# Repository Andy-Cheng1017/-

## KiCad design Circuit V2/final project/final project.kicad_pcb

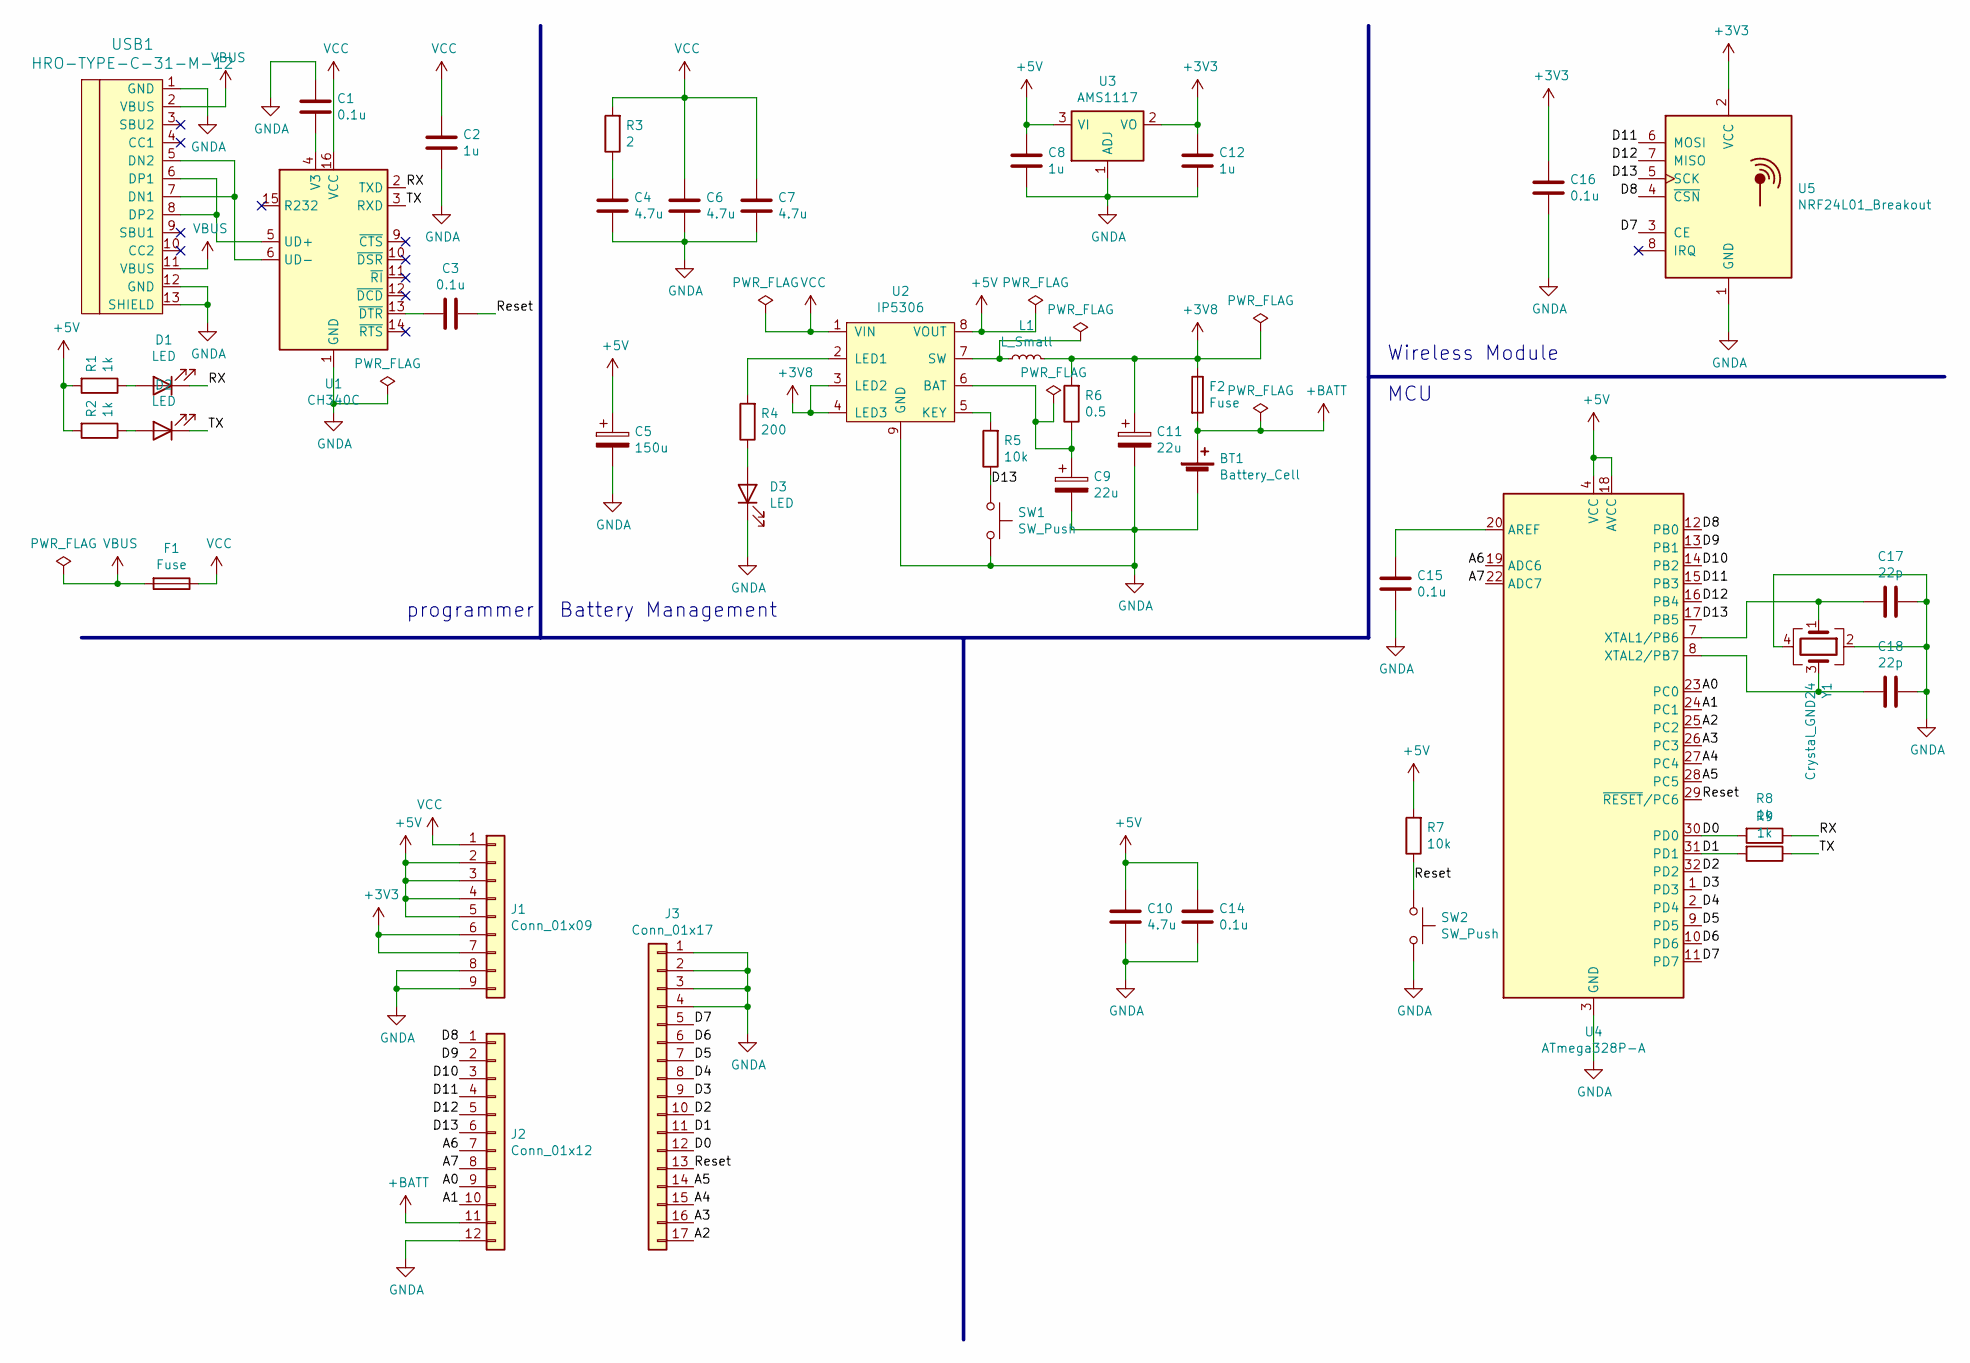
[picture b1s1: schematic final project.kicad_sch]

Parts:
BT1: Battery_Cell; BatteryHolder_MPD_BH-18650-PC2
C1, C3, C14, C15, C16: 0.1u; C_0805_2012Metric
C2, C8, C12: 1u; C_0805_2012Metric
C4, C6, C7, C10: 4.7u; C_0805_2012Metric
C5: 150u; CP_EIA-7343-15_Kemet-W
C9, C11: 22u; CP_EIA-7343-15_Kemet-W
C17, C18: 22p; C_0805_2012Metric
D1, D2, D3: LED; LED_0805_2012Metric
F1, F2: Fuse; Fuse_1812_4532Metric
J1: Conn_01x09; PinHeader_1x09_P2.54mm_Vertical
J2: Conn_01x12; PinHeader_1x12_P2.54mm_Vertical
J3: Conn_01x17; PinHeader_1x17_P2.54mm_Vertical
L1: L_Small; L_Bourns_SRN6045TA
R1, R2, R8, R9: 1k; R_0805_2012Metric
R3: 2; R_0805_2012Metric
R4: 200; R_0805_2012Metric
R5, R7: 10k; R_0805_2012Metric
R6: 0.5; R_0805_2012Metric
SW1, SW2: SW_Push; SW_SPST_CK_RS282G05A3
U1: CH340C; SOIC-16_3.9x9.9mm_P1.27mm
U2: IP5306; SOIC-8-1EP_3.9x4.9mm_P1.27mm_EP2.29x3mm_ThermalVias
U3: AMS1117; SOT-223-3_TabPin2
U4: ATmega328P-A; TQFP-32_7x7mm_P0.8mm
U5: NRF24L01_Breakout; NRF24L01-SMD
USB1: HRO-TYPE-C-31-M-12
Y1: Crystal_GND24; Crystal_SMD_3225-4Pin_3.2x2.5mm

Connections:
+3V3: C12.2, C16.2, J1.6, J1.7, U3.2 (VO), U5.2 (VCC)
+3V8: C11.1, F2.1, L1.2, R6.2, U2.3 (LED2), U2.4 (LED3)
+5V: C5.1, C8.2, C10.2, C14.2, J1.2, J1.3, J1.4, J1.5, R1.2, R2.2, R7.2, U2.8 (VOUT), U3.3 (VI), U4.4 (VCC), U4.6 (VCC), U4.18 (AVCC)
+BATT: BT1.1 (+), F2.2, J2.11
/A0: J2.9, U4.23 (PC0)
/A1: J2.10, U4.24 (PC1)
/A2: J3.17, U4.25 (PC2)
/A3: J3.16, U4.26 (PC3)
/A4: J3.15, U4.27 (PC4)
/A5: J3.14, U4.28 (PC5)
/A6: J2.7, U4.19 (ADC6)
/A7: J2.8, U4.22 (ADC7)
/D0: J3.12, R8.2, U4.30 (PD0)
/D1: J3.11, R9.2, U4.31 (PD1)
/D2: J3.10, U4.32 (PD2)
/D3: J3.9, U4.1 (PD3)
/D4: J3.8, U4.2 (PD4)
/D5: J3.7, U4.9 (PD5)
/D6: J3.6, U4.10 (PD6)
/D7: J3.5, U4.11 (PD7), U5.3 (CE)
/D8: J2.1, U4.12 (PB0), U5.4 (~CSN)
/D9: J2.2, U4.13 (PB1)
/D10: J2.3, U4.14 (PB2)
/D11: J2.4, U4.15 (PB3), U5.6 (MOSI)
/D12: J2.5, U4.16 (PB4), U5.7 (MISO)
/D13: J2.6, R5.1, SW1.1, U4.17 (PB5), U5.5 (SCK)
/RX: D1.1 (K), R8.1, U1.2 (TXD)
/Reset: C3.1, J3.13, R7.1, SW2.1, U4.29 (~RESET/PC6)
/TX: D2.1 (K), R9.1, U1.3 (RXD)
GNDA: BT1.2 (-), C1.2, C2.1, C4.1, C5.2, C6.1, C7.1, C8.1, C9.2, C10.1, C11.2, C12.1, C14.1, C15.1, C16.1, C17.1, C18.1, D3.1 (K), J1.8, J1.9, J2.12, J3.1, J3.2, J3.3, J3.4, SW1.2, SW2.2, U1.1 (GND), U2.9 (GND), U3.1 (ADJ), U4.3 (GND), U4.5 (GND), U4.21 (GND), U5.1 (GND), USB1.1 (GND), USB1.12 (GND), USB1.13 (SHIELD), Y1.2, Y1.4
unnamed: C1.1, U1.4 (V3)
unnamed: C3.2, U1.13 (~DTR)
unnamed: C4.2, R3.1
unnamed: C9.1, R6.1, U2.6 (BAT)
unnamed: C15.2, U4.20 (AREF)
unnamed: C17.2, U4.7 (XTAL1/PB6), Y1.1
unnamed: C18.2, U4.8 (XTAL2/PB7), Y1.3
unnamed: D1.2 (A), R1.1
unnamed: D2.2 (A), R2.1
unnamed: D3.2 (A), R4.1
unnamed: L1.1, U2.7 (SW)
unnamed: R4.2, U2.2 (LED1)
unnamed: R5.2, U2.5 (KEY)
unnamed: U1.5 (UD+), USB1.6 (DP1), USB1.8 (DP2)
unnamed: U1.6 (UD-), USB1.5 (DN2), USB1.7 (DN1)
VBUS: F1.2, USB1.2 (VBUS), USB1.11 (VBUS)
VCC: C2.2, C6.2, C7.2, F1.1, J1.1, R3.2, U1.16 (VCC), U2.1 (VIN)

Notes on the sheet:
MCU
programmer
Wireless Module
Battery Management

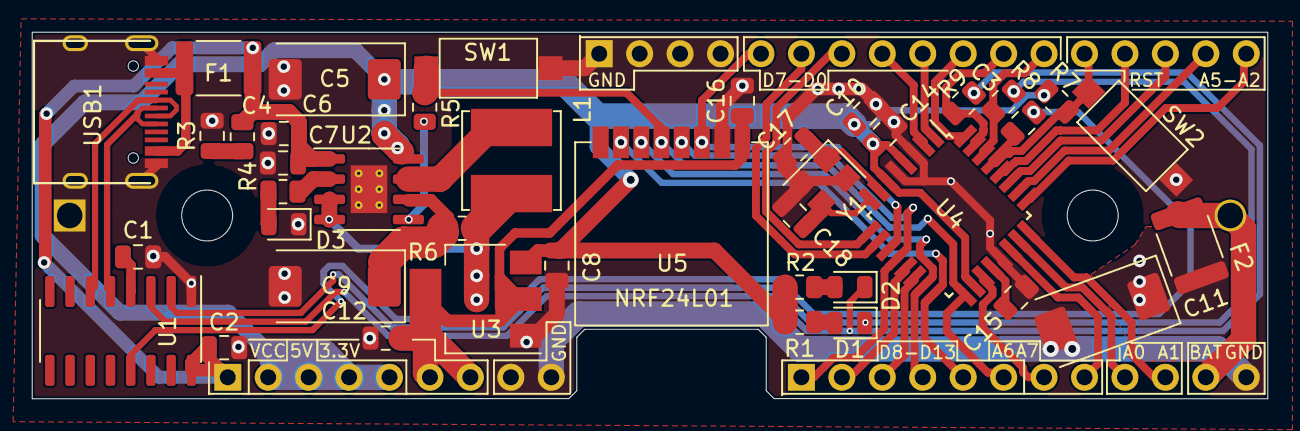
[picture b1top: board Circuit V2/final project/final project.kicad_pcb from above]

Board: 2 copper layers, 77.6 x 23.0 mm, 45 parts (1 on the bottom side), 47 nets.

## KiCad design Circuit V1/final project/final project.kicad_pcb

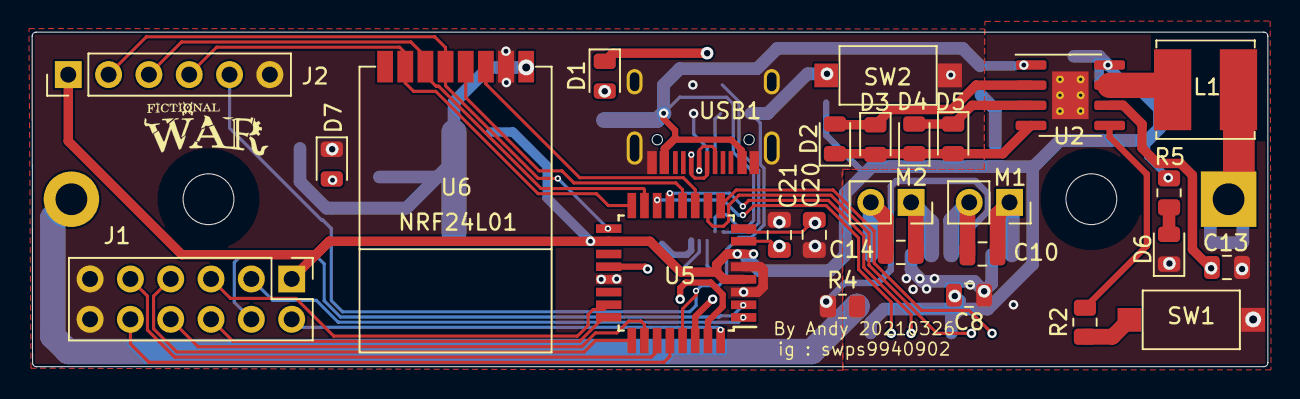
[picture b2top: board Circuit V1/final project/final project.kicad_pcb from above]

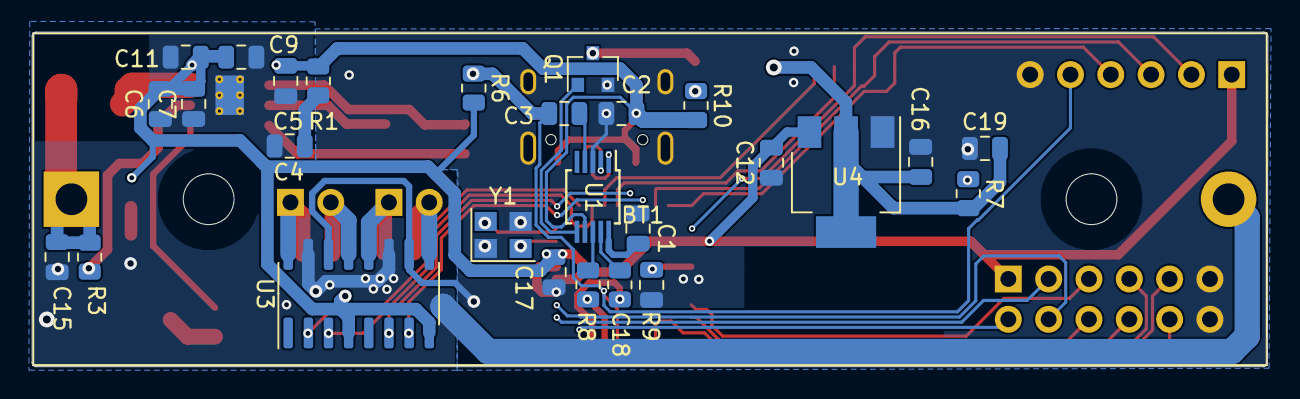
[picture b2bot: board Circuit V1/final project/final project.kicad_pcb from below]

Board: 2 copper layers, 77.8 x 21.1 mm, 55 parts (28 on the bottom side), 53 nets.

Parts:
BT1: Battery_Cell; BatteryHolder_MPD_BH-18650-PC2
C1, C3, C18: 0.1u; C_0805_2012Metric
C2, C4, C5, C17: 10u; C_0805_2012Metric
C6, C7, C9, C11, C13, C15: 22u; C_0805_2012Metric
C8, C10, C12, C14, C16, C19: 1u; C_0805_2012Metric
C20, C21: 22p; C_0805_2012Metric
D1, D2, D3, D4, D5, D6, D7: LED; LED_0805_2012Metric
J1: Conn_01x12; PinHeader_2x06_P2.54mm_Vertical
J2: Conn_01x06; PinHeader_1x06_P2.54mm_Vertical
L1: L_Small; L_Bourns_SRN6045TA
M1, M2: Motor_DC; PinSocket_1x02_P2.54mm_Vertical
Q1: 2N7002; SOT-23
R1: 2; R_0805_2012Metric
R2, R6: 10k; R_0805_2012Metric
R3: 0.5; R_0805_2012Metric
R4: 0; R_0805_2012Metric
R5, R8, R9, R10: 1k; R_0805_2012Metric
R7: 500; R_0805_2012Metric
SW1, SW2: SW_Push; SW_SPST_CK_RS282G05A3
U1: CH340E; MSOP-10_3x3mm_P0.5mm
U2: IP5306; SOIC-8-1EP_3.9x4.9mm_P1.27mm_EP2.29x3mm_ThermalVias
U3: FM1208S; SOIC-16_3.9x9.9mm_P1.27mm
U4: AMS1117-3.3; SOT-223-3_TabPin2
U5: ATmega328P-AU; TQFP-32_7x7mm_P0.8mm
U6: NRF24L01_Breakout; NRF24L01-SMD
USB1: HRO-TYPE-C-31-M-12
Y1: Crystal_GND24; Crystal_SMD_3225-4Pin_3.2x2.5mm

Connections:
+3V3: C16.2, C19.2, R7.2, U4.2, U6.2
+5V: C6.2, C7.2, C8.2, C9.2, C11.2, C12.2, C17.2, J1.1, J2.1, R5.2, R6.2, U2.8, U3.4, U3.8, U4.3, U5.4, U5.6, U5.18
/A0: J1.5, U5.23
/A1: J1.6, U5.24
/A2: J1.7, U5.25
/A3: J1.8, U5.26
/A4: J1.9, U5.27
/A5: J1.10, U5.28
/CE: U5.11, U6.3
/CSN: U5.12, U6.4
/D2: J1.2, U5.32
/D3: J1.3, U5.1
/D4: J1.4, U5.2
/INA: U3.2, U5.9
/INB: U3.3, U5.10
/INC: U3.6, U5.13
/IND: U3.7, U5.14
/MISO: J2.4, U5.16, U6.7
/MOSI: J2.3, U5.15, U6.6
/OUTA: C10.2, M1.1, U3.16
/OUTB: C10.1, M1.2, U3.13
/OUTC: C14.2, M2.1, U3.12
/OUTD: C14.1, M2.2, U3.9
/RX: R8.1, U1.8
/Reset: C3.1, J2.5, R6.1, SW2.1, U5.29
/SCK: J2.2, U5.17, U6.5
/TX: R9.1, U1.9
GND: BT1.2, C4.1, C5.1, C6.1, C7.1, C8.1, C9.1, C11.1, C13.2, C15.2, D6.1, R4.2, SW1.2, U2.9, U3.11, U3.15
GNDA: C1.2, C2.1, C12.1, C16.1, C17.1, C18.1, C19.1, C20.1, C21.1, D7.1, J1.11, J1.12, J2.6, Q1.2, R4.1, SW2.2, U1.3, U3.10, U3.14, U4.1, U5.3, U5.5, U5.21, U6.1, USB1.1, USB1.12, USB1.13, Y1.1, Y1.3
unnamed: BT1.1, C15.1, L1.2, R3.2
unnamed: C1.1, U1.10
unnamed: C3.2, U1.4
unnamed: C4.2, R1.1
unnamed: C13.1, R3.1, U2.6
unnamed: C18.2, U5.20
unnamed: C20.2, U5.7, Y1.2
unnamed: C21.2, U5.8, Y1.4
unnamed: D1.1, Q1.3
unnamed: D1.2, R10.1
unnamed: D2.1, D3.2, D4.1, D5.2, U2.4
unnamed: D2.2, D3.1, U2.2
unnamed: D4.2, D5.1, U2.3
unnamed: D6.2, R5.1
unnamed: D7.2, R7.1
unnamed: L1.1, U2.7
unnamed: Q1.1, U1.6
unnamed: R2.1, SW1.1
unnamed: R2.2, U2.5
unnamed: R8.2, U5.30
unnamed: R9.2, U5.31
unnamed: U1.1, USB1.6, USB1.8
unnamed: U1.2, USB1.5, USB1.7
VCC: C2.2, C5.2, R1.2, R10.2, U1.7, U2.1, USB1.2, USB1.11

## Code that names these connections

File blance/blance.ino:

#include <PID_v1.h>
#include "I2Cdev.h"
#include "MPU6050_6Axis_MotionApps_V6_12.h"
#include "RF24.h"
#if I2CDEV_IMPLEMENTATION == I2CDEV_ARDUINO_WIRE
#include "Wire.h"
#endif

#define INTERRUPT_PIN 2  // use pin 2 on Arduino Uno & most boards
#define LeftMotorDirection 1 //the spin of the left motor(top view)，1 is clockwise, 0 is counterclockwise
#define RightMotorDirection 0 //the spin of the right motor(top view)，1 is clockwise, 0 is counterclockwise
#define INA 5
#define INB 6
#define INC 9
#define IND 10
int Kp = 90;
int Ki = 300;
int Kd = 2;
#define target -50
//-----------------------------------------------------------------------
double Setpoint, Input, Output;
PID PIDCTRL(&Input, &Output, &Setpoint, Kp, Ki, Kd, DIRECT);
byte Reverse, Forward;

//-----------------------------------------------------------------------
MPU6050 mpu;
Quaternion q;           // [w, x, y, z]         quaternion container
VectorFloat gravity;    // [x, y, z]            gravity vector
bool dmpReady = false;  // set true if DMP init was successful
uint8_t mpuIntStatus;   // holds actual interrupt status byte from MPU
uint8_t devStatus;      // return status after each device operation (0 = success, !0 = error)
uint16_t packetSize;    // expected DMP packet size (default is 42 bytes)
uint16_t fifoCount;     // count of all bytes currently in FIFO
uint8_t fifoBuffer[64]; // FIFO storage buffer
float ypr[3];           // [yaw, pitch, roll]   yaw/pitch/roll container and gravity vector
//---------------------------------------------------------------------------------------------- -
volatile bool mpuInterrupt = false;     // indicates whether MPU interrupt pin has gone high
void dmpDataReady() {
  mpuInterrupt = true;
}
//---------------------------------------------------------------------------------------------- -
RF24 rf24(7, 8);                                  //(ce,cs)
const byte pipe = 1;                              // 指定通道編號
const byte addr[] = "1Node";                      //Address
//-----------------------------------------------------------------------------
int msg[4];                  //主要接收訊息變數 4byte 32bite
//所有馬達狀態

unsigned long CurrentTime ;          //設定起始時間ms
unsigned long TimeOut;               //最終時間ms

//float CurrentAngle;

void setup() {
  //  delay(5000);
#if I2CDEV_IMPLEMENTATION == I2CDEV_ARDUINO_WIRE
  Wire.begin();
  Wire.setClock(400000); // 400kHz I2C clock. Comment this line if having compilation difficulties
#elif I2CDEV_IMPLEMENTATION == I2CDEV_BUILTIN_FASTWIRE
  Fastwire::setup(400, true);
#endif
  //  Serial.begin(115200);
  //  while (!Serial); // wait for Leonardo enumeration, others continue immediately
  mpu.initialize();
  pinMode(INTERRUPT_PIN, INPUT);
  devStatus = mpu.dmpInitialize();
  mpu.setXGyroOffset(37);
  mpu.setYGyroOffset(51);
  mpu.setZGyroOffset(-12);
  mpu.setXAccelOffset(-1418);
  mpu.setYAccelOffset(219);
  mpu.setZAccelOffset(1000);
  mpu.setDMPEnabled(true);
  if (devStatus == 0) {
    mpu.setDMPEnabled(true);
    attachInterrupt(digitalPinToInterrupt(INTERRUPT_PIN), dmpDataReady, RISING);
    mpuIntStatus = mpu.getIntStatus();
    dmpReady = true;
    packetSize = mpu.dmpGetFIFOPacketSize();
  } else {
    // ERROR!
    // 1 = initial memory load failed
    // 2 = DMP configuration updates failed
    // (if it's going to break, usually the code will be 1)
    //    Serial.print(F("DMP Initialization failed (code "));
    //    Serial.print(devStatus);
    //    Serial.println(F(")"));
  }
  //-----------------------------------------------------------------------------------------
  Setpoint = target;
  PIDCTRL.SetMode(AUTOMATIC);
  PIDCTRL.SetSampleTime(1);
  PIDCTRL.SetOutputLimits(-255, 255);
  //-----------------------------------------------------------------------------------------
  pinMode(INA, OUTPUT);
  pinMode(INB, OUTPUT);
  pinMode(INC, OUTPUT);
  pinMode(IND, OUTPUT);
  rf24.begin();
  rf24.setChannel(83);               // 設定頻道編號
  rf24.openWritingPipe(addr);  // 開啟通道和位址
  rf24.openReadingPipe(1, addr);
  rf24.startListening();               // 開始監聽無線廣播
  rf24.setPALevel(RF24_PA_MAX);      //設最高功率接收
  rf24.setDataRate(RF24_2MBPS) ;
  //  rf24.setPayloadSize(16);
  //-----------------------------------------------------------------------------------------

  //  while (millis() - CurrentTime <= 10000) {
  //    if (mpu.dmpGetCurrentFIFOPacket(fifoBuffer)) { // Get the Latest packet
  //      mpu.dmpGetQuaternion(&q, fifoBuffer);
  //      mpu.dmpGetGravity(&gravity, &q);
  //      mpu.dmpGetYawPitchRoll(ypr, &q, &gravity);
  //      //      Serial.print("ypr\t");
  //      //      Serial.print(ypr[0] * 180 / M_PI);
  //      //      Serial.print("\t");
  //      //      Serial.print(ypr[1] * 180 / M_PI);
  //      //      Serial.print("\t");
  //      //      Serial.print(ypr[2] * 180 / M_PI);
  //      //      Serial.println();
  //    }
  //  }

}

void loop() {
  rf24.read(&msg , sizeof(msg));
  if (rf24.available(&pipe)) {
    rf24.read(&msg , sizeof(msg));
    rf24.stopListening();
    rf24.write(&msg, sizeof(msg));
    rf24.startListening();
    PIDCTRL.SetTunings(msg[0], msg[1], msg[2]);
    PIDCTRL.SetPoint(msg[3]);
  }
  PIDCTRL.Compute();
  mpu.dmpGetCurrentFIFOPacket(fifoBuffer);
  mpu.dmpGetQuaternion(&q, fifoBuffer);
  mpu.dmpGetGravity(&gravity, &q);
  mpu.dmpGetYawPitchRoll(ypr, &q, &gravity);
  Input = ypr[1] * 180 / M_PI;
  //  Serial.print(Input);
  //  Serial.print("\t");
  //  Serial.println(Output);
  if (Output >= 1) {
    Reverse = abs(Output);
    analogWrite(INA, Reverse * RightMotorDirection);
    analogWrite(INB, Reverse * !RightMotorDirection);
    analogWrite(INC, Reverse * LeftMotorDirection);
    analogWrite(IND, Reverse * !LeftMotorDirection);
  }
  else if (Output < 1) {
    Forward = abs(Output);
    analogWrite(INA, Forward * !RightMotorDirection);
    analogWrite(INB, Forward * RightMotorDirection);
    analogWrite(INC, Forward * !LeftMotorDirection);
    analogWrite(IND, Forward * LeftMotorDirection);
  }
}
